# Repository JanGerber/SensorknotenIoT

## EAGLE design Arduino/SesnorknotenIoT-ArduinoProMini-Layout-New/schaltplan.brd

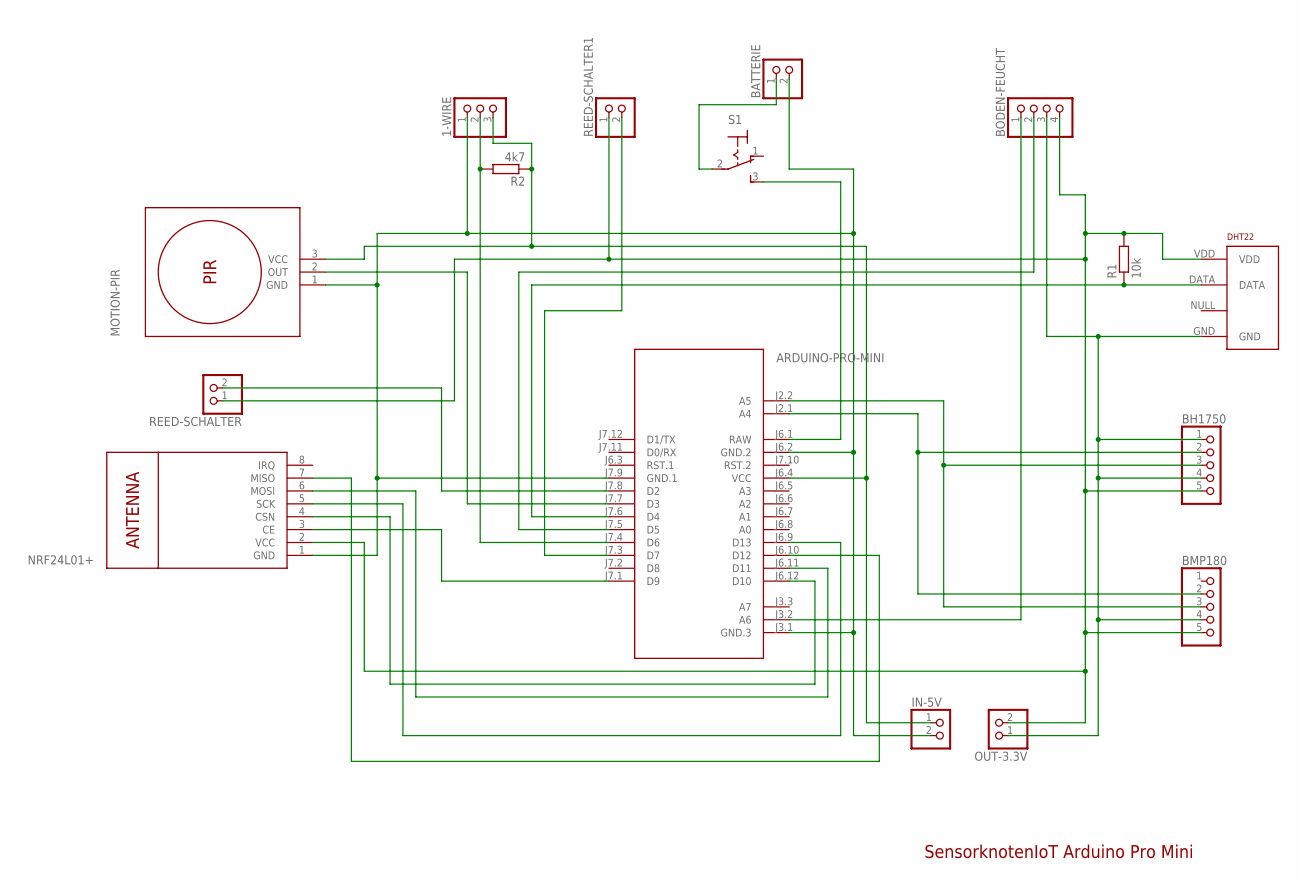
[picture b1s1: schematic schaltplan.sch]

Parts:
1-WIRE: PINHD-1X3; 1X03
ARDUINO-PRO-MINI: ARDUINO-PRO-MINI-5.0V#NP; ARDUINO-PRO-MINI#NP
BATTERIE: PINHD-1X2; 1X02
BH1750: PINHD-1X5; 1X05
BMP180: PINHD-1X5; 1X05
BODEN-FEUCHT: PINHD-1X4; 1X04
DHT22: RHT03_DHT-22_AM2302; RHT03_DHT-22
IN-5V: PINHD-1X2; 1X02
MOTION-PIR: MOTION-PIR-DYP-ME003
NRF24L01+: WIRELESS-NRF24L01
OUT-3.3V: PINHD-1X2; 1X02
R1: 10k; 0207/10
R2: 4k7; 0207/10
REED-SCHALTER, REED-SCHALTER1: PINHD-1X2; 1X02
S1: 320-916

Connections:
3.3V: BH1750.5, BMP180.5, BODEN-FEUCHT.4, DHT22.VDD, NRF24L01+.2 (VCC), OUT-3.3V.2, R1.2, REED-SCHALTER.1, REED-SCHALTER1.1
GND: 1-WIRE.1, ARDUINO-PRO-MINI.J3.1 (GND.3), ARDUINO-PRO-MINI.J6.2 (GND.2), ARDUINO-PRO-MINI.J7.9 (GND.1), BATTERIE.2, BH1750.1, BH1750.4, BMP180.4, BODEN-FEUCHT.3, DHT22.GND, IN-5V.2, MOTION-PIR.1 (GND), NRF24L01+.1 (GND), OUT-3.3V.1
IN-3.3V: 1-WIRE.3, ARDUINO-PRO-MINI.J6.4 (VCC), IN-5V.1, MOTION-PIR.3 (VCC), R2.1
unnamed: ARDUINO-PRO-MINI.J6.1 (RAW), S1.3 (S)
unnamed: BATTERIE.1, S1.2
unnamed: ARDUINO-PRO-MINI.J7.5 (D5), BODEN-FEUCHT.2
unnamed: ARDUINO-PRO-MINI.J7.6 (D4), DHT22.DATA, R1.1
unnamed: 1-WIRE.2, ARDUINO-PRO-MINI.J7.4 (D6), R2.2
unnamed: ARDUINO-PRO-MINI.J3.2 (A6), BODEN-FEUCHT.1
unnamed: ARDUINO-PRO-MINI.J7.3 (D7), REED-SCHALTER1.2
unnamed: ARDUINO-PRO-MINI.J7.7 (D3), MOTION-PIR.2 (OUT)
unnamed: ARDUINO-PRO-MINI.J7.8 (D2), REED-SCHALTER.2
unnamed: ARDUINO-PRO-MINI.J2.1 (A4), BH1750.2, BMP180.2
unnamed: ARDUINO-PRO-MINI.J2.2 (A5), BH1750.3, BMP180.3
unnamed: ARDUINO-PRO-MINI.J7.1 (D9), NRF24L01+.3 (CE)
unnamed: ARDUINO-PRO-MINI.J6.12 (D10), NRF24L01+.4 (CSN)
unnamed: ARDUINO-PRO-MINI.J6.9 (D13), NRF24L01+.5 (SCK)
unnamed: ARDUINO-PRO-MINI.J6.11 (D11), NRF24L01+.6 (MOSI)
unnamed: ARDUINO-PRO-MINI.J6.10 (D12), NRF24L01+.7 (MISO)

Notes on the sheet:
SensorknotenIoT Arduino Pro Mini

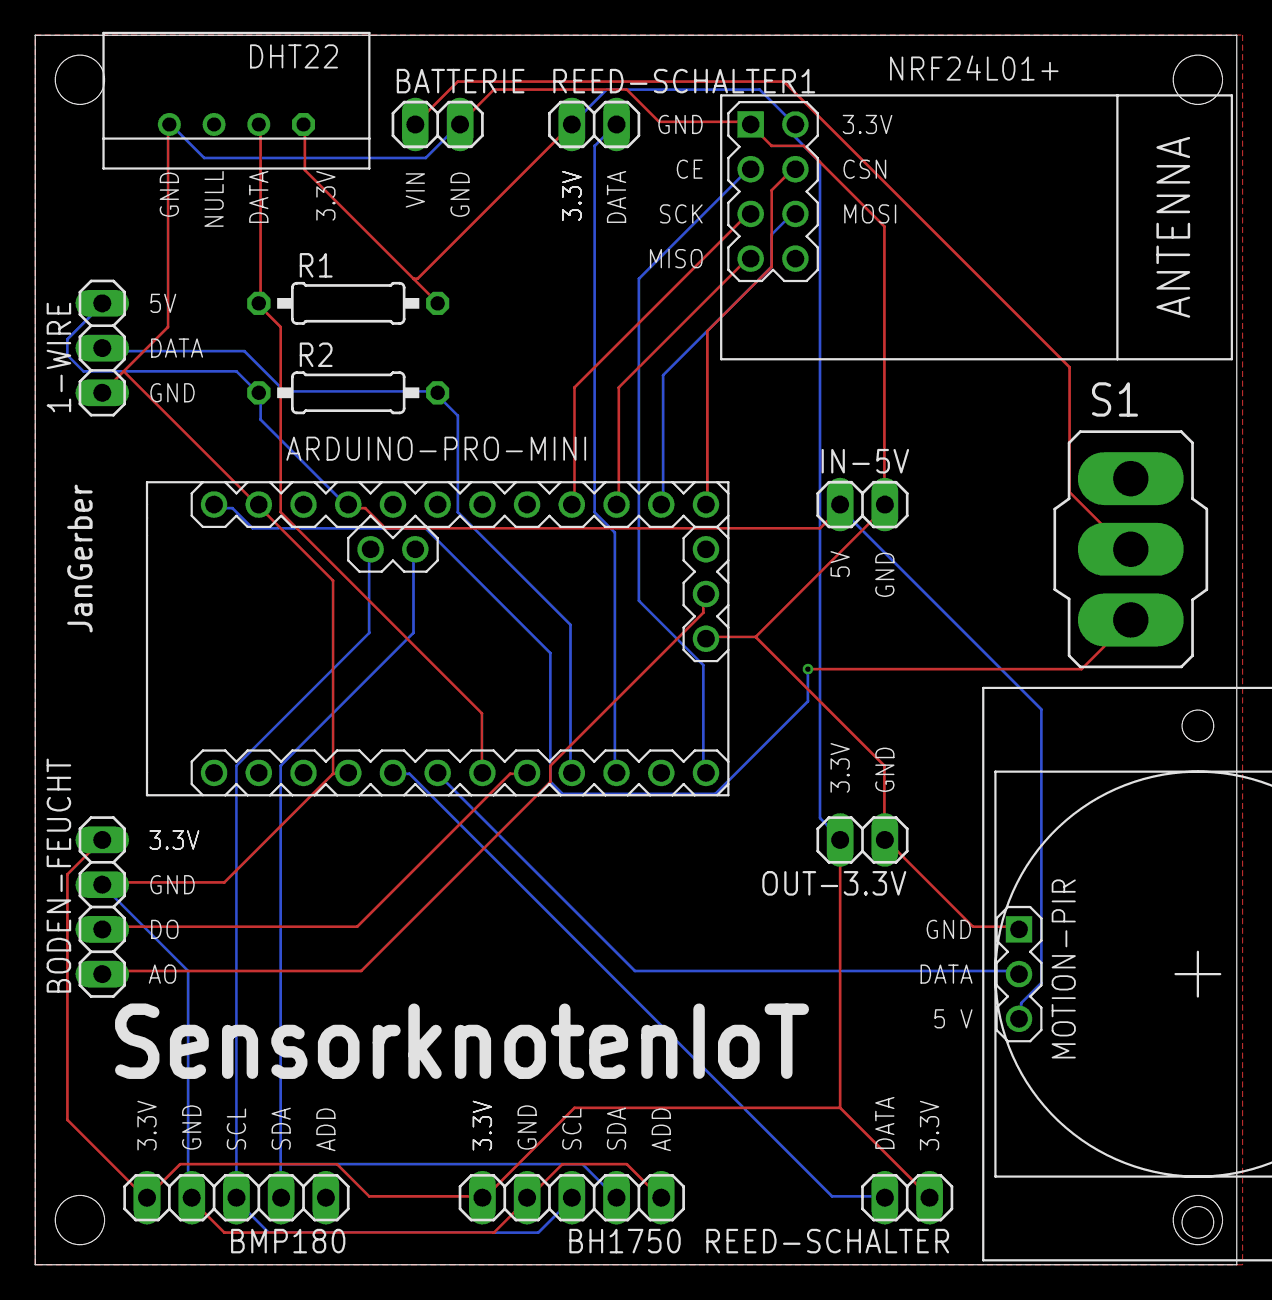
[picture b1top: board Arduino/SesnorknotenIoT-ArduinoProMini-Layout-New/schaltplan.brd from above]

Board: 2 copper layers, 68.2 x 69.8 mm, 16 parts (0 on the bottom side), 19 nets.

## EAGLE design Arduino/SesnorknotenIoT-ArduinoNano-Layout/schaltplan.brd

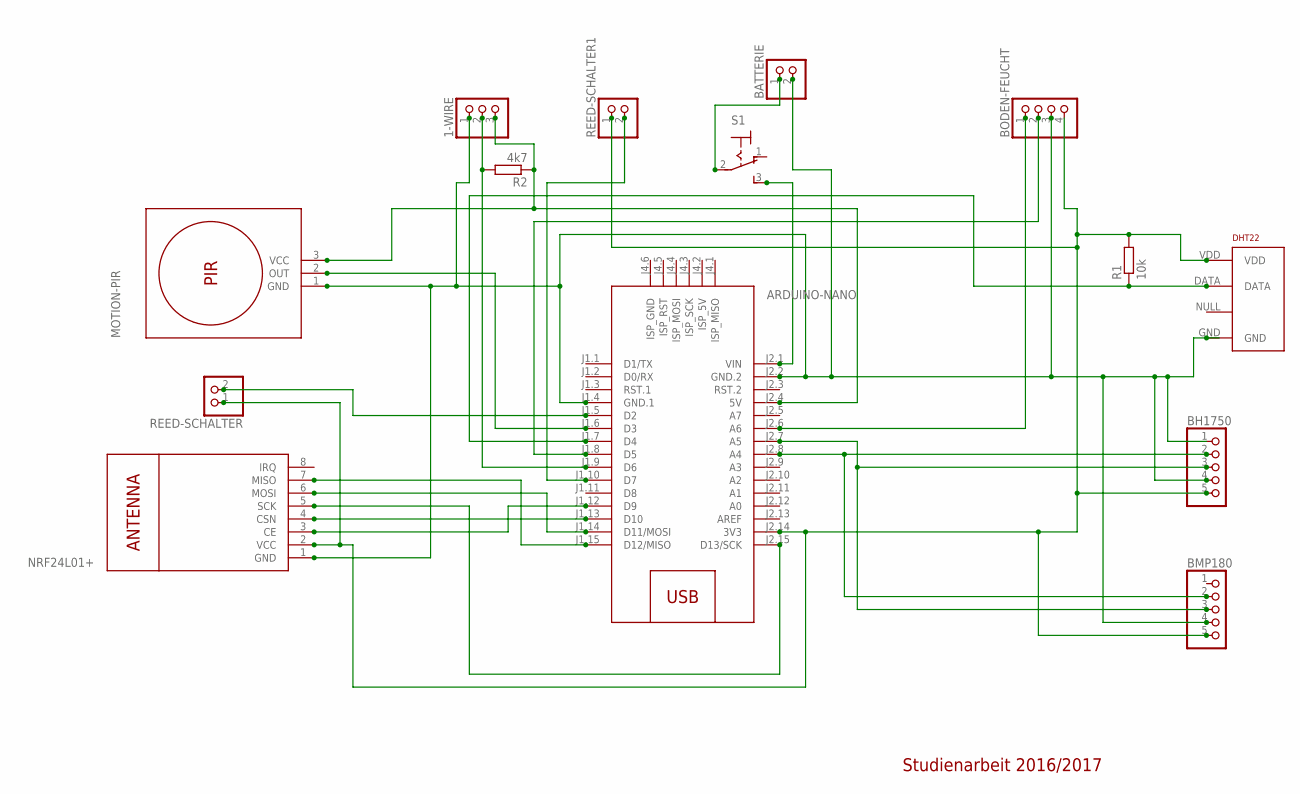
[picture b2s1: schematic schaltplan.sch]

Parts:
1-WIRE: PINHD-1X3; 1X03
ARDUINO-NANO: ARDUINO-NANO-3.0#ISP
BATTERIE: PINHD-1X2; 1X02
BH1750: PINHD-1X5; 1X05
BMP180: PINHD-1X5; 1X05
BODEN-FEUCHT: PINHD-1X4; 1X04
DHT22: RHT03_DHT-22_AM2302; RHT03_DHT-22
MOTION-PIR: MOTION-PIR-DYP-ME003
NRF24L01+: WIRELESS-NRF24L01
R1: 10k; 0207/10
R2: 4k7; 0207/10
REED-SCHALTER, REED-SCHALTER1: PINHD-1X2; 1X02
S1: 320-916

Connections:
3.3V: ARDUINO-NANO.J2.14 (3V3), BH1750.5, BMP180.5, BODEN-FEUCHT.4, DHT22.VDD, NRF24L01+.2 (VCC), R1.2, REED-SCHALTER.1, REED-SCHALTER1.1
5V: 1-WIRE.3, ARDUINO-NANO.J2.4 (5V), MOTION-PIR.3 (VCC), R2.1
GND: 1-WIRE.1, ARDUINO-NANO.J1.4 (GND.1), ARDUINO-NANO.J2.2 (GND.2), BATTERIE.2, BH1750.1, BH1750.4, BMP180.4, BODEN-FEUCHT.3, DHT22.GND, MOTION-PIR.1 (GND), NRF24L01+.1 (GND)
MISO: ARDUINO-NANO.J1.15 (D12/MISO), NRF24L01+.7 (MISO)
MOSI: ARDUINO-NANO.J1.14 (D11/MOSI), NRF24L01+.6 (MOSI)
unnamed: ARDUINO-NANO.J1.7 (D4), DHT22.DATA, R1.1
unnamed: ARDUINO-NANO.J1.5 (D2), REED-SCHALTER.2
unnamed: ARDUINO-NANO.J2.6 (A6), BODEN-FEUCHT.1
unnamed: ARDUINO-NANO.J1.8 (D5), BODEN-FEUCHT.2
unnamed: BATTERIE.1, S1.2
unnamed: 1-WIRE.2, ARDUINO-NANO.J1.9 (D6), R2.2
unnamed: ARDUINO-NANO.J1.10 (D7), REED-SCHALTER1.2
unnamed: ARDUINO-NANO.J1.6 (D3), MOTION-PIR.2 (OUT)
unnamed: ARDUINO-NANO.J1.12 (D9), NRF24L01+.3 (CE)
unnamed: ARDUINO-NANO.J1.13 (D10), NRF24L01+.4 (CSN)
unnamed: ARDUINO-NANO.J2.1 (VIN), S1.3 (S)
SCK: ARDUINO-NANO.J2.15 (D13/SCK), NRF24L01+.5 (SCK)
SCL: ARDUINO-NANO.J2.7 (A5), BH1750.3, BMP180.3
SDA: ARDUINO-NANO.J2.8 (A4), BH1750.2, BMP180.2

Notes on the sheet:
Studienarbeit 2016/2017

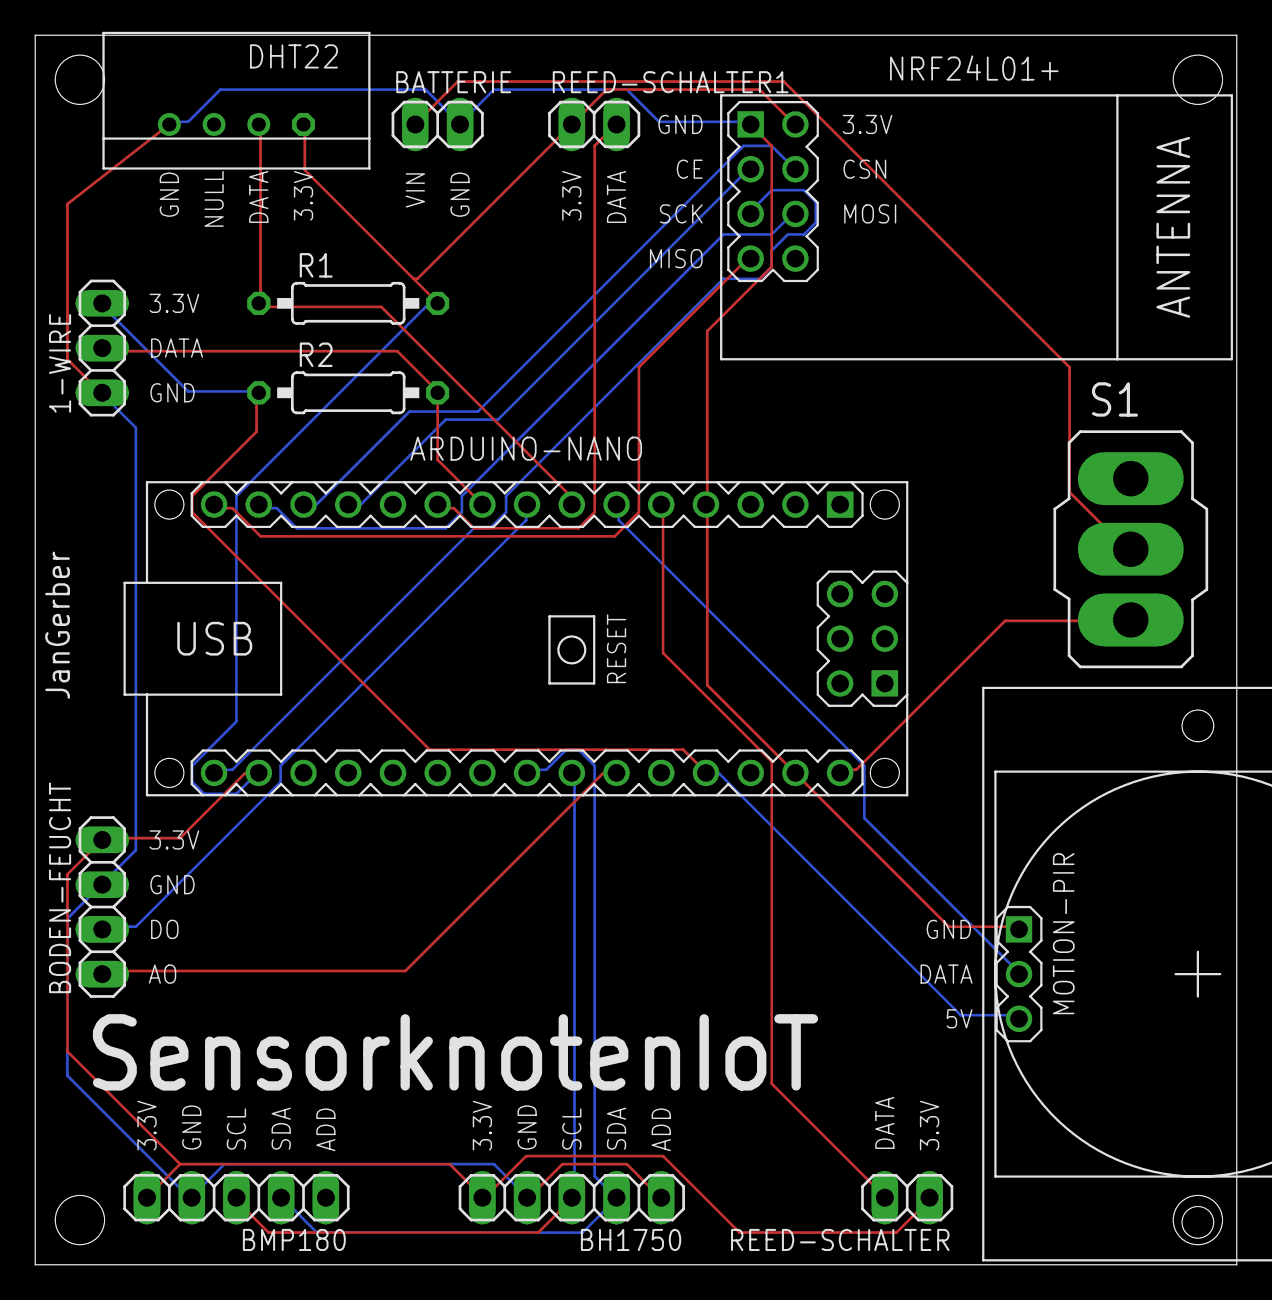
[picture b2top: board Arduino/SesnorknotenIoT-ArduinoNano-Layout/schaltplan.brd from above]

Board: 2 copper layers, 68.2 x 69.8 mm, 14 parts (0 on the bottom side), 19 nets.

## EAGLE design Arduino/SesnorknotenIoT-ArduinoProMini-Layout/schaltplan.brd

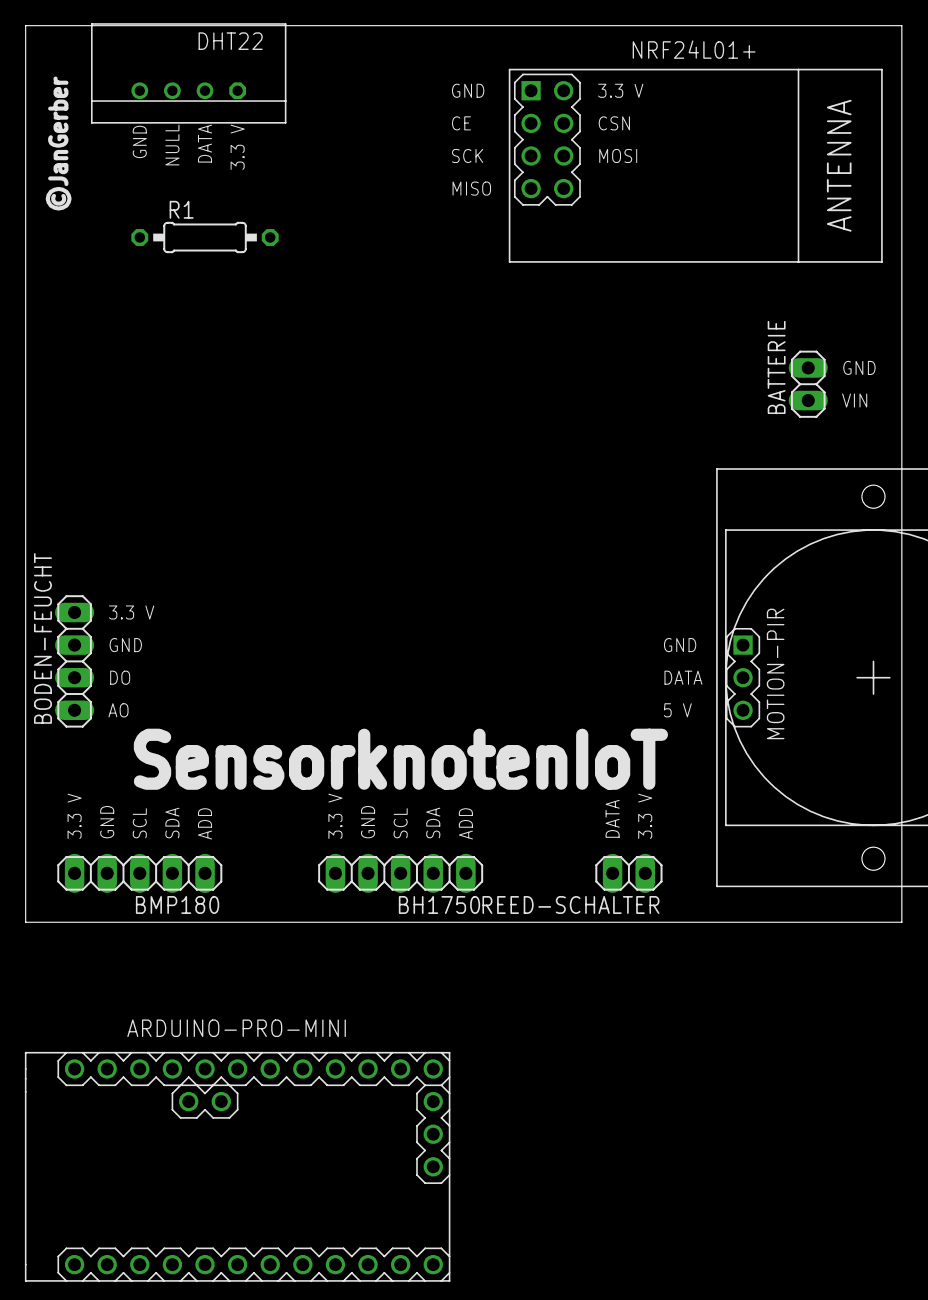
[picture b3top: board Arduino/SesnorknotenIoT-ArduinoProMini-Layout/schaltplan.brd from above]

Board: 2 copper layers, 68.2 x 69.8 mm, 10 parts (0 on the bottom side), 3 nets, no tracks yet.

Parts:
ARDUINO-PRO-MINI: ARDUINO-PRO-MINI#NP
BATTERIE: 1X02
BH1750: 1X05
BMP180: 1X05
BODEN-FEUCHT: 1X04
DHT22: RHT03_DHT-22
MOTION-PIR: MOTION-PIR-DYP-ME003
NRF24L01+: WIRELESS-NRF24L01
R1: 10k; 0207/10
REED-SCHALTER: 1X02

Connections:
GND: ARDUINO-PRO-MINI.J6.2, BATTERIE.2, BH1750.1, BH1750.4, BMP180.4, BODEN-FEUCHT.3, DHT22.GND, MOTION-PIR.1, NRF24L01+.1
RAW: ARDUINO-PRO-MINI.J6.1, BATTERIE.1
VCC: ARDUINO-PRO-MINI.J6.4, MOTION-PIR.3, NRF24L01+.2

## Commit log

2016-10-20 Init
2016-10-21 Anpassungen Arduino sender
2016-10-23 Low Power - Stromsparmodus Arduino
2016-10-24 EEPROM dauerhaftes Speichern des Timers
2016-10-24 AES Implementation
2016-10-25 aes anpassungen
2016-10-26 Neue AES Libarary
2016-10-26 Fertigstellung AES
2016-10-27 Pinbelegung DHT22
2016-10-28 Entfernen überflüssiger Bibliotheken -Arduino_Reciever
2016-11-11 Sensorknoten Schaltplan und Layout
2016-11-13 Eagle +Reed Schalter +1-Wire +Schalter stromversorgung
2016-11-18 Änderungen Sender Verschlüsselung und Encodierung
2016-12-05 Encodierung der Uebertragung
2017-02-13 Sensorkonten - Mesh Algorithmus
2017-02-14 Problem behoben: EEPROM Read and Write
2017-02-14 Timer Interrupt hinzugefügt
2017-02-14 Id Arduino - EEPROM
2017-02-15 Anpassungen Daten Paket: +Last-Hop Addr +Ausgabe eines gesamten Pakets
2017-02-15 Paket erhalten Message
2017-02-21 Anpassungen Libs und Fehlerbehebung Pipes
2017-02-21 - Nicht benötigte Pipes - Debug Informationen
2017-02-21 Sensor Added
2017-03-01 Encodierung der Nachrichten hinzugefuegt (Base64)
2017-03-02 Anpassungen Sensoren +Bewegungsmelder +nur Auswertung wenn die Sensoren angeschlossen sind
2017-03-02 Pro Mini - Energiesparen
2017-03-07 Schaltplan für Arduino Pro Mini geändert Energiesparmodus aktivierbar
2017-03-07 Libraries
2017-03-13 Reed Kontakt Sensor - verschiedene Anpassungen
2017-03-14 Energiesparmodus & Debug Ausgabe
2017-03-22 Fehlerbehebung OneWire
2017-05-14 Finaler Commit

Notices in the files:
Arduino/SesnorknotenIoT-ArduinoProMini-Layout/schaltplan.brd:
©JanGerber
parts and their libraries:
diy-modules: Released under the Creative Commons Attribution 4.0 International License: http://creativecommons.org/licenses/by/4.0
SparkFun-Aesthetics: Licensing: Creative Commons ShareAlike 4.0 International - https://creativecommons.org/licenses/by-sa/4.0
